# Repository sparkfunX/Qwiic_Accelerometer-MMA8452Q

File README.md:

Qwiic Accelerometer - MMA8452Q
========================================

[*SPX-14248*](https://www.sparkfun.com/products/14248)

License Information
-------------------

This product is _**open source**_!

Please review the LICENSE.md file for license information.

If you have any questions or concerns on licensing, please contact techsupport@sparkfun.com.

Distributed as-is; no warranty is given.

- Your friends at SparkFun.

_<COLLABORATION CREDIT>_

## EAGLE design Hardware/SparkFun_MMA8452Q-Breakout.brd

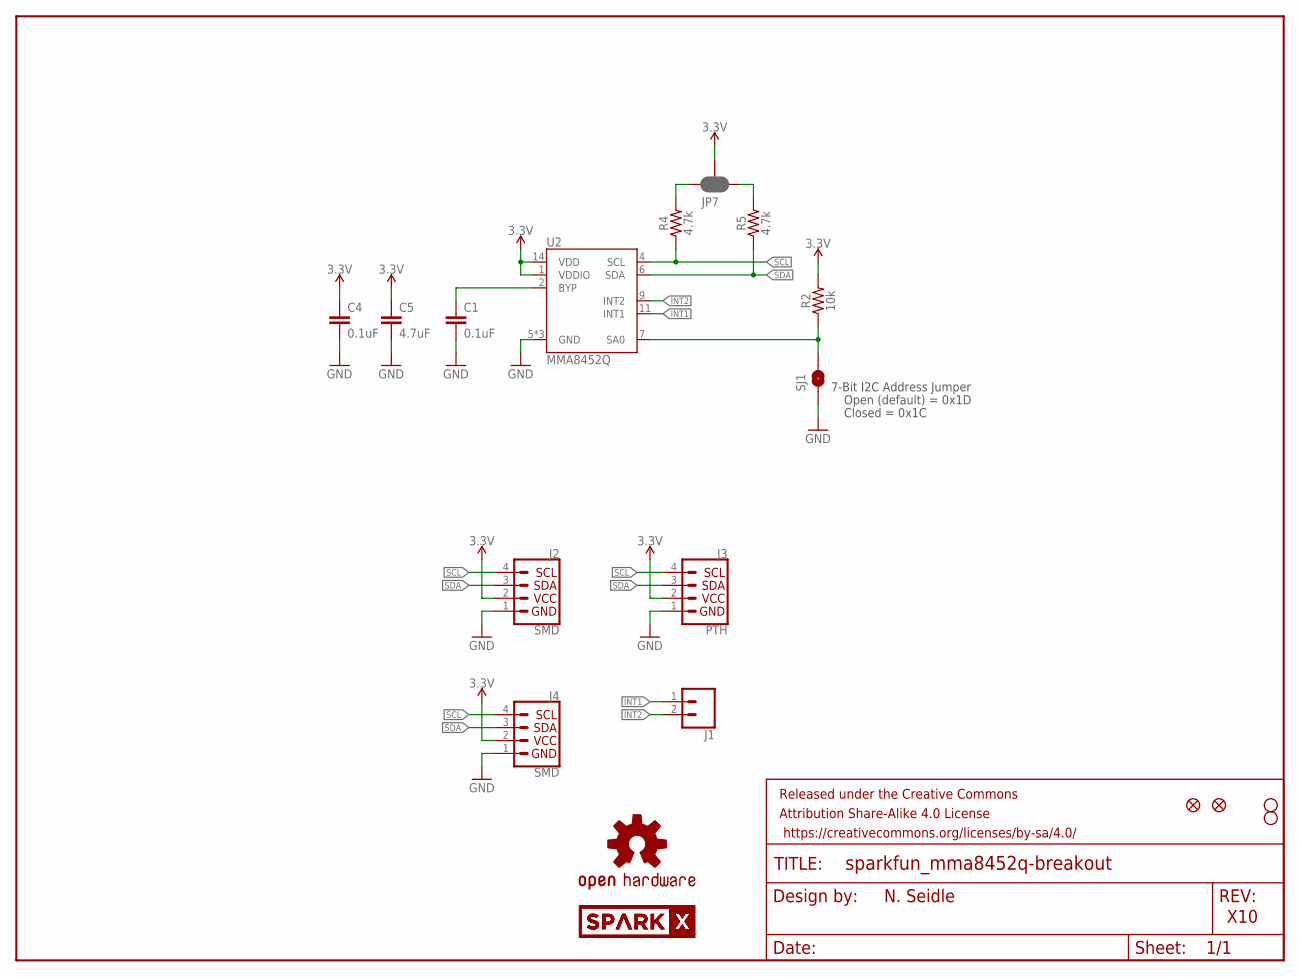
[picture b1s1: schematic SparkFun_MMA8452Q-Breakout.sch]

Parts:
C1, C4: 0.1uF; 0603
C5: 4.7uF; 0603
FRAME1: FRAME-LETTER; CREATIVE_COMMONS
J1: CONN_021X02_NO_SILK; 1X02_NO_SILK
J2, J4: SMD; 1X04_1MM_RA
J3: PTH; 1X04_NO_SILK
JP2, JP6: FIDUCIALUFIDUCIAL; MICRO-FIDUCIAL
JP3, JP4: STAND-OFF
JP7: JUMPER-SMT_3_2-NC_PASTE_SILK; SMT-JUMPER_3_2-NC_PASTE_SILK
LOGO1: OSHW-LOGOMINI; OSHW-LOGO-MINI
R2: 10k; 0603
R4, R5: 4.7k; 0603
SJ1: SOLDERJUMPERNO; SJ_2S-NO
U2: MMA8452Q; QFN-16_0.5MM
U$1, U$2: SPARKX-LOGO4; SPARKX-MEDIUM

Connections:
3.3V: C4.1, C5.1, J2.2 (VCC), J3.2 (VCC), J4.2 (VCC), JP7.2, R2.2, U2.1 (VDDIO), U2.14 (VDD)
BYP: C1.1, U2.2 (BYP)
GND: C1.2, C4.2, C5.2, J2.1 (GND), J3.1 (GND), J4.1 (GND), SJ1.1, U2.5 (GND), U2.10 (GND), U2.12 (GND)
INT1: J1.1, U2.11 (INT1)
INT2: J1.2, U2.9 (INT2)
unnamed: JP7.1, R5.2
unnamed: JP7.3, R4.2
SA0: R2.1, SJ1.2, U2.7 (SA0)
SCL: J2.4 (SCL), J3.4 (SCL), J4.4 (SCL), R4.1, U2.4 (SCL)
SDA: J2.3 (SDA), J3.3 (SDA), J4.3 (SDA), R5.1, U2.6 (SDA)

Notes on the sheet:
7-Bit I2C Address Jumper
Closed = 0x1C
Open (default) = 0x1D
N. Seidle
X10

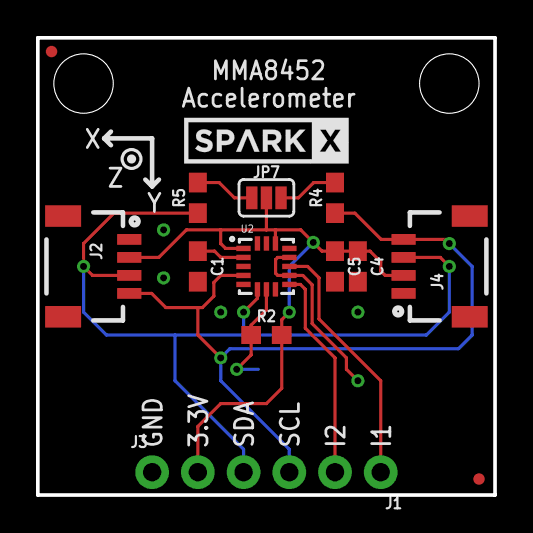
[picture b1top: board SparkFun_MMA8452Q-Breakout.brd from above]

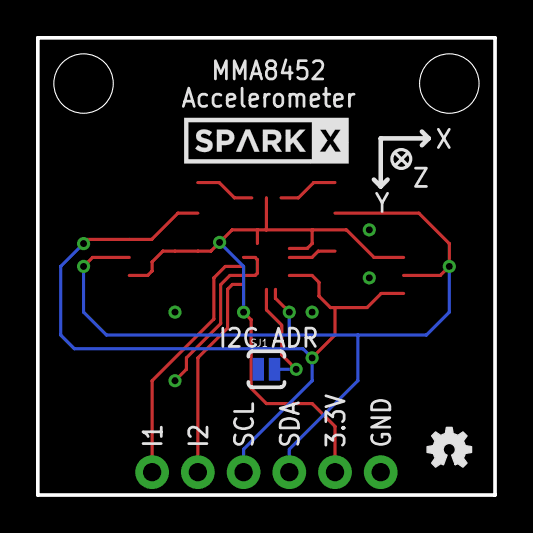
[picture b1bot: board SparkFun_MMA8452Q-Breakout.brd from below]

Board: 2 copper layers, 25.4 x 25.4 mm, 21 parts (3 on the bottom side), 10 nets.

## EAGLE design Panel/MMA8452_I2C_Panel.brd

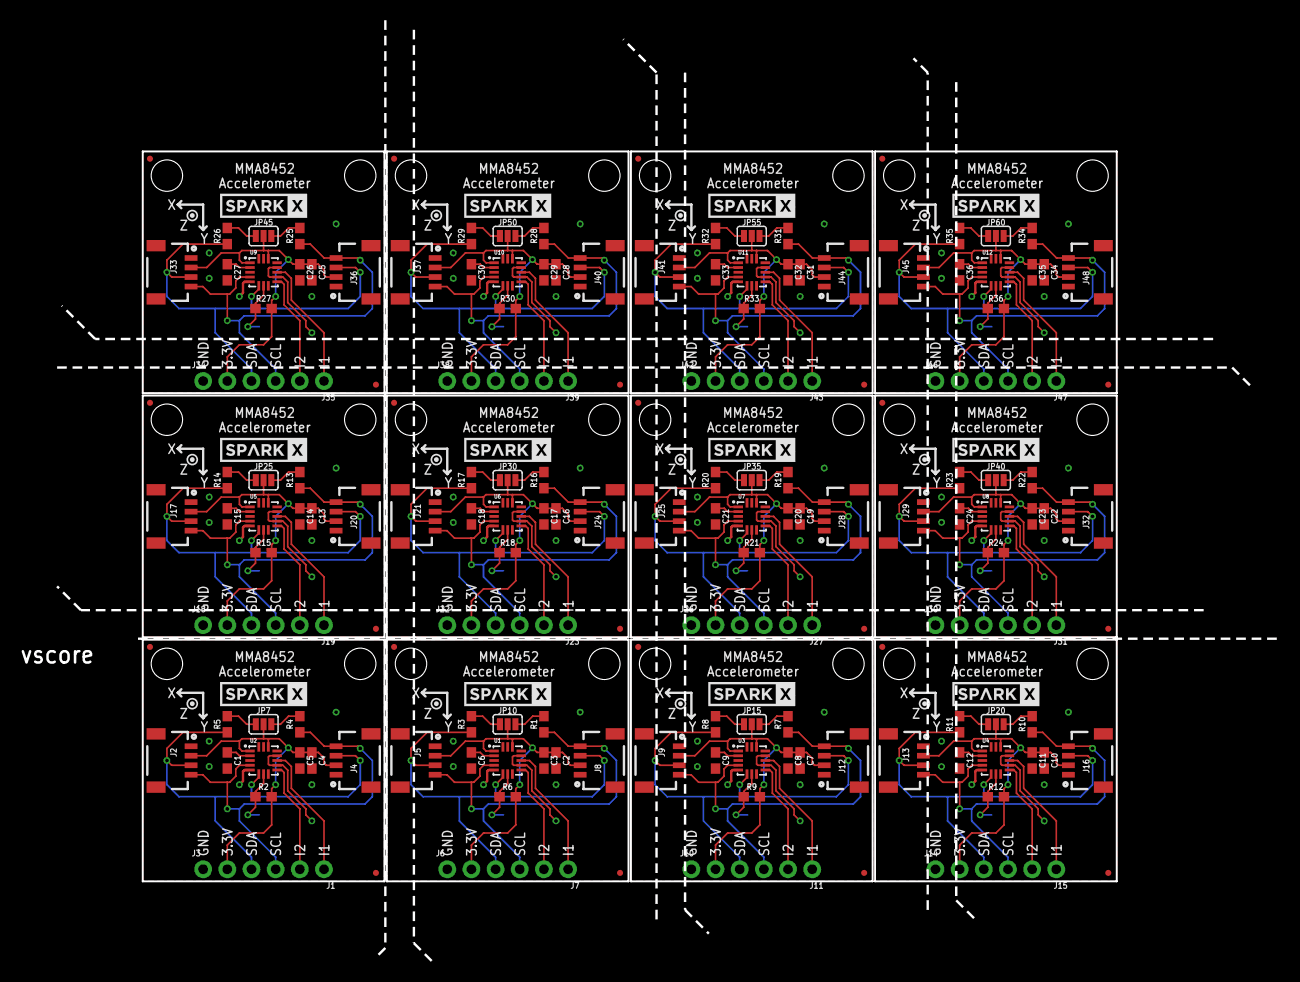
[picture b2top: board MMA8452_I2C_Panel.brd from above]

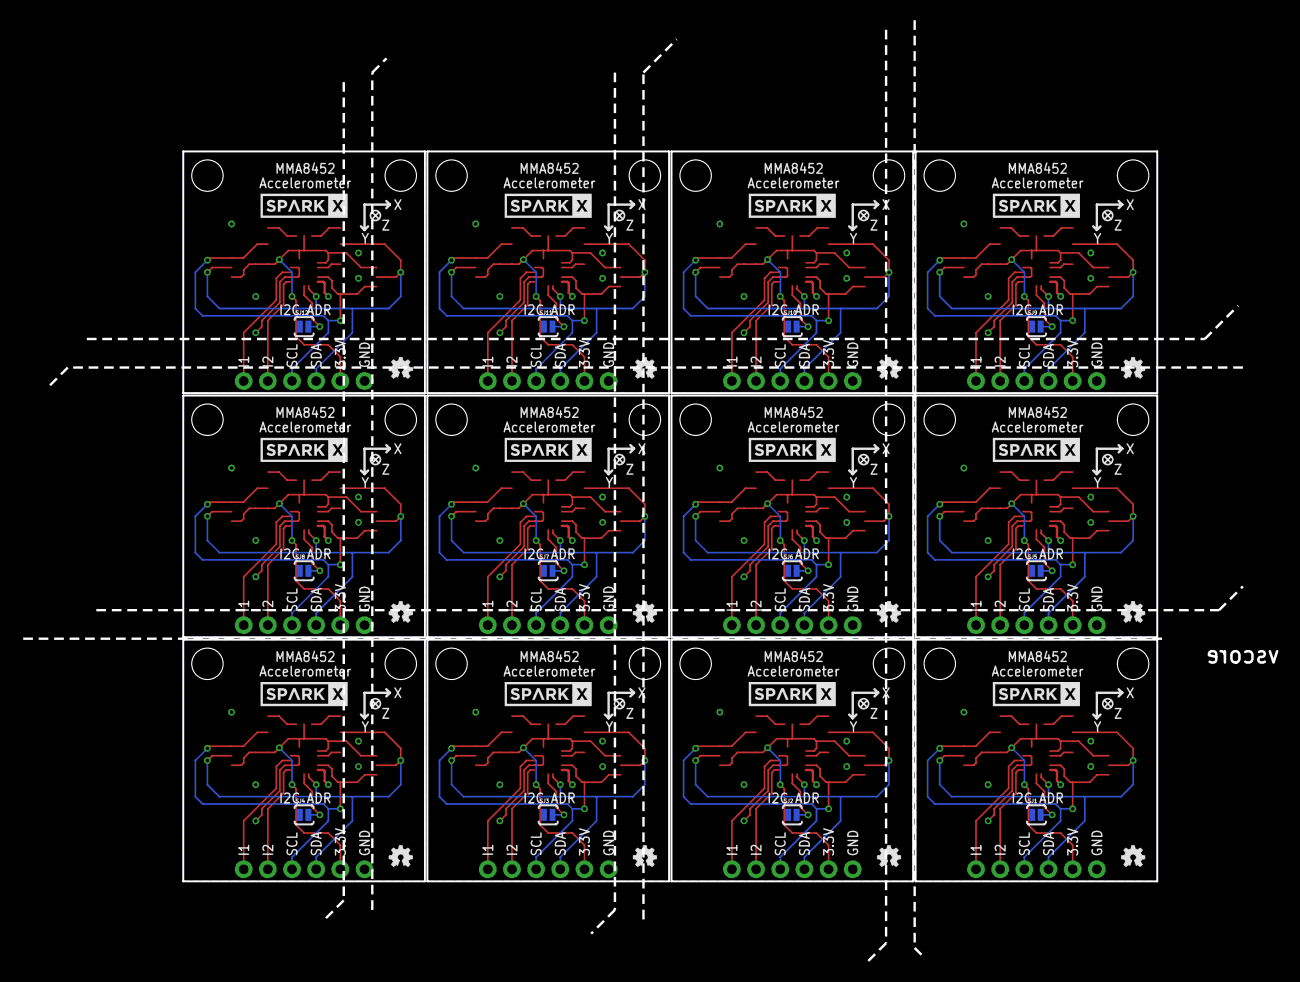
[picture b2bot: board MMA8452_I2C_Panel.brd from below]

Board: 2 copper layers, 128.5 x 99.0 mm, 240 parts (36 on the bottom side), 120 nets.

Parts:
C1, C2, C4, C6, C7, C9, C10, C12, C13, C15, C16, C18, C19, C21, C22, C24, C25, C27, C28, C30, C31, C33, C34, C36: 0.1uF; 0603
C3, C5, C8, C11, C14, C17, C20, C23, C26, C29, C32, C35: 4.7uF; 0603
J1, J7, J11, J15, J19, J23, J27, J31, J35, J39, J43, J47: 1X02_NO_SILK
J2, J4, J5, J8, J9, J12, J13, J16, J17, J20, J21, J24, J25, J28, J29, J32, J33, J36, J37, J40, J41, J44, J45, J48: SMD; 1X04_1MM_RA
J3, J6, J10, J14, J18, J22, J26, J30, J34, J38, J42, J46: PTH; 1X04_NO_SILK
JP1, JP3, JP4, JP5, JP11, JP12, JP16, JP17, JP21, JP22, JP26, JP27, JP31, JP32, JP36, JP37, JP41, JP42, JP46, JP47, JP51, JP52, JP56, JP57: STAND-OFF
JP2, JP6, JP8, JP9, JP13, JP14, JP18, JP19, JP23, JP24, JP28, JP29, JP33, JP34, JP38, JP39, JP43, JP44, JP48, JP49, JP53, JP54, JP58, JP59: FIDUCIALUFIDUCIAL; MICRO-FIDUCIAL
JP7, JP10, JP15, JP20, JP25, JP30, JP35, JP40, JP45, JP50, JP55, JP60: SMT-JUMPER_3_2-NC_PASTE_SILK
LOGO1, LOGO2, LOGO3, LOGO4, LOGO5, LOGO6, LOGO7, LOGO8, LOGO9, LOGO10, LOGO11, LOGO12: OSHW-LOGOMINI; OSHW-LOGO-MINI
R1, R3, R4, R5, R7, R8, R10, R11, R13, R14, R16, R17, R19, R20, R22, R23, R25, R26, R28, R29, R31, R32, R34, R35: 4.7k; 0603
R2, R6, R9, R12, R15, R18, R21, R24, R27, R30, R33, R36: 10k; 0603
SJ1, SJ2, SJ3, SJ4, SJ5, SJ6, SJ7, SJ8, SJ9, SJ10, SJ11, SJ12: SJ_2S-NO
U1, U2, U3, U4, U5, U6, U7, U8, U9, U10, U11, U12: MMA8452Q; QFN-16_0.5MM
U$1, U$2, U$3, U$4, U$5, U$6, U$7, U$8, U$9, U$10, U$11, U$12, U$13, U$14, U$15, U$16, U$17, U$18, U$19, U$20, U$21, U$22, U$23, U$24: SPARKX-LOGO4; SPARKX-MEDIUM

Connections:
3.3V: C4.1, C5.1, J2.2, J3.2, J4.2, JP7.2, R2.2, U2.1, U2.14
3.3V1: C2.1, C3.1, J5.2, J6.2, J8.2, JP10.2, R6.2, U1.1, U1.14
3.3V2: C7.1, C8.1, J9.2, J10.2, J12.2, JP15.2, R9.2, U3.1, U3.14
3.3V3: C10.1, C11.1, J13.2, J14.2, J16.2, JP20.2, R12.2, U4.1, U4.14
3.3V4: C13.1, C14.1, J17.2, J18.2, J20.2, JP25.2, R15.2, U5.1, U5.14
3.3V5: C16.1, C17.1, J21.2, J22.2, J24.2, JP30.2, R18.2, U6.1, U6.14
3.3V6: C19.1, C20.1, J25.2, J26.2, J28.2, JP35.2, R21.2, U7.1, U7.14
3.3V7: C22.1, C23.1, J29.2, J30.2, J32.2, JP40.2, R24.2, U8.1, U8.14
3.3V8: C25.1, C26.1, J33.2, J34.2, J36.2, JP45.2, R27.2, U9.1, U9.14
3.3V9: C28.1, C29.1, J37.2, J38.2, J40.2, JP50.2, R30.2, U10.1, U10.14
3.3V10: C31.1, C32.1, J41.2, J42.2, J44.2, JP55.2, R33.2, U11.1, U11.14
3.3V11: C34.1, C35.1, J45.2, J46.2, J48.2, JP60.2, R36.2, U12.1, U12.14
BYP: C1.1, U2.2
BYP1: C6.1, U1.2
BYP2: C9.1, U3.2
BYP3: C12.1, U4.2
BYP4: C15.1, U5.2
BYP5: C18.1, U6.2
BYP6: C21.1, U7.2
BYP7: C24.1, U8.2
BYP8: C27.1, U9.2
BYP9: C30.1, U10.2
BYP10: C33.1, U11.2
BYP11: C36.1, U12.2
GND: C1.2, C4.2, C5.2, J2.1, J3.1, J4.1, SJ1.1, U2.5, U2.10, U2.12
GND1: C2.2, C3.2, C6.2, J5.1, J6.1, J8.1, SJ2.1, U1.5, U1.10, U1.12
GND2: C7.2, C8.2, C9.2, J9.1, J10.1, J12.1, SJ3.1, U3.5, U3.10, U3.12
GND3: C10.2, C11.2, C12.2, J13.1, J14.1, J16.1, SJ4.1, U4.5, U4.10, U4.12
GND4: C13.2, C14.2, C15.2, J17.1, J18.1, J20.1, SJ5.1, U5.5, U5.10, U5.12
GND5: C16.2, C17.2, C18.2, J21.1, J22.1, J24.1, SJ6.1, U6.5, U6.10, U6.12
GND6: C19.2, C20.2, C21.2, J25.1, J26.1, J28.1, SJ7.1, U7.5, U7.10, U7.12
GND7: C22.2, C23.2, C24.2, J29.1, J30.1, J32.1, SJ8.1, U8.5, U8.10, U8.12
GND8: C25.2, C26.2, C27.2, J33.1, J34.1, J36.1, SJ9.1, U9.5, U9.10, U9.12
GND9: C28.2, C29.2, C30.2, J37.1, J38.1, J40.1, SJ10.1, U10.5, U10.10, U10.12
GND10: C31.2, C32.2, C33.2, J41.1, J42.1, J44.1, SJ11.1, U11.5, U11.10, U11.12
GND11: C34.2, C35.2, C36.2, J45.1, J46.1, J48.1, SJ12.1, U12.5, U12.10, U12.12
INT1: J1.1, U2.11
INT2: J1.2, U2.9
INT3: J7.2, U1.9
INT4: J7.1, U1.11
INT5: J11.2, U3.9
INT6: J11.1, U3.11
INT7: J15.2, U4.9
INT8: J15.1, U4.11
INT9: J19.2, U5.9
INT10: J19.1, U5.11
INT11: J23.2, U6.9
INT12: J23.1, U6.11
INT13: J27.2, U7.9
INT14: J27.1, U7.11
INT15: J31.2, U8.9
INT16: J31.1, U8.11
INT17: J35.2, U9.9
INT18: J35.1, U9.11
INT19: J39.2, U10.9
INT20: J39.1, U10.11
INT21: J43.2, U11.9
INT22: J43.1, U11.11
INT23: J47.2, U12.9
INT24: J47.1, U12.11
unnamed: JP7.1, R5.2
unnamed: JP7.3, R4.2
unnamed: JP10.1, R3.2
unnamed: JP10.3, R1.2
unnamed: JP15.1, R8.2
unnamed: JP15.3, R7.2
unnamed: JP20.1, R11.2
unnamed: JP20.3, R10.2
unnamed: JP25.1, R14.2
unnamed: JP25.3, R13.2
unnamed: JP30.1, R17.2
unnamed: JP30.3, R16.2
unnamed: JP35.1, R20.2
unnamed: JP35.3, R19.2
unnamed: JP40.1, R23.2
unnamed: JP40.3, R22.2
unnamed: JP45.1, R26.2
unnamed: JP45.3, R25.2
unnamed: JP50.1, R29.2
unnamed: JP50.3, R28.2
unnamed: JP55.1, R32.2
unnamed: JP55.3, R31.2
unnamed: JP60.1, R35.2
unnamed: JP60.3, R34.2
SA0: R2.1, SJ1.2, U2.7
SA1: R6.1, SJ2.2, U1.7
SA2: R9.1, SJ3.2, U3.7
SA3: R12.1, SJ4.2, U4.7
SA4: R15.1, SJ5.2, U5.7
SA5: R18.1, SJ6.2, U6.7
SA6: R21.1, SJ7.2, U7.7
SA7: R24.1, SJ8.2, U8.7
SA8: R27.1, SJ9.2, U9.7
SA9: R30.1, SJ10.2, U10.7
SA10: R33.1, SJ11.2, U11.7
SA11: R36.1, SJ12.2, U12.7
SCL: J2.4, J3.4, J4.4, R4.1, U2.4
SCL1: J5.4, J6.4, J8.4, R1.1, U1.4
SCL2: J9.4, J10.4, J12.4, R7.1, U3.4
SCL3: J13.4, J14.4, J16.4, R10.1, U4.4
SCL4: J17.4, J18.4, J20.4, R13.1, U5.4
SCL5: J21.4, J22.4, J24.4, R16.1, U6.4
SCL6: J25.4, J26.4, J28.4, R19.1, U7.4
SCL7: J29.4, J30.4, J32.4, R22.1, U8.4
SCL8: J33.4, J34.4, J36.4, R25.1, U9.4
SCL9: J37.4, J38.4, J40.4, R28.1, U10.4
SCL10: J41.4, J42.4, J44.4, R31.1, U11.4
SCL11: J45.4, J46.4, J48.4, R34.1, U12.4
SDA: J2.3, J3.3, J4.3, R5.1, U2.6
SDA1: J5.3, J6.3, J8.3, R3.1, U1.6
SDA2: J9.3, J10.3, J12.3, R8.1, U3.6
SDA3: J13.3, J14.3, J16.3, R11.1, U4.6
SDA4: J17.3, J18.3, J20.3, R14.1, U5.6
SDA5: J21.3, J22.3, J24.3, R17.1, U6.6
SDA6: J25.3, J26.3, J28.3, R20.1, U7.6
SDA7: J29.3, J30.3, J32.3, R23.1, U8.6
SDA8: J33.3, J34.3, J36.3, R26.1, U9.6
SDA9: J37.3, J38.3, J40.3, R29.1, U10.6
SDA10: J41.3, J42.3, J44.3, R32.1, U11.6
SDA11: J45.3, J46.3, J48.3, R35.1, U12.6

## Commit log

2017-03-08 :confetti_ball: Added .gitattributes & .gitignore files
2017-03-08 Added a GND via. Created 3mm spaced panel.
2017-03-31 Adding berbers
    Note: added new berbers for stencil but this order still did not line
    up with 2mil gaps.
2017-03-31 File rename
2017-09-06 Reducing panel size to 3x3
2018-03-06 Backlink to CADLAB.io has been added.

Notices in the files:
parts and their libraries:
SparkFun-Resistors: Licensing: Creative Commons ShareAlike 4.0 International - https://creativecommons.org/licenses/by-sa/4.0
SparkFun-Aesthetics: Released under the Creative Commons Attribution Share-Alike 4.0 License
SparkFun-Aesthetics: https://creativecommons.org/licenses/by-sa/4.0
